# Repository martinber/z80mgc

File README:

z80mgc
======

z80 minimal game console

```
~/extra/async/programas/zasm-4.4.10-Linux64/zasm ./../../src/test.asm -l ./../../out/test.lst -o ./../../out/test.bin -uw; cargo run -- ../../out/test.bin
```

Clock speed
-----------

- RAM is 71256 SA25TPG. Therefore is 25ns access time: Data is valid 25ns after OE and CS are set.
- RAM is 28C64 25P. Therefore I think it is 250ns access time: Data is valid 250ns after OE and CS are set.
- CPU is Z84C0006TPG. Therefore is 6.17MHz, equivalent to 166ns per clock. It waits memory for 2
  clock cycles (this time is shortened a bit because of the logic gates I use to select memory).
- LCD takes 1.6ms for clearing and 72 µs (72000ns) for each of the other instructions. So I can do
  around 13800 instructions per second. When writing make the E pulse at least 160ns long (CPU does
  this for around 2 clock cycles) and leave the data for 20ns after disabling (CPU does this for
  around half a clock cycle). When reading, data is valid 260ns after enabled (CPU waits for around
  2 clock cycles)
- Logic gates have around 10ns propagation time.
- The nake game was doing around 150 instructions per game loop. If I consider 4 clocks per
  instruction, I can run it at 60fps if the clock is at around 36kHz?

So apparently I can run at full clock speed, where I would be close to reaching the limit of LCD
read times. I have to wait LCD after each instruction.

Other display options
---------------------

* LCD with HD44780: http://6502.org/mini-projects/optrexlcd/lcd.htm

* LCD with ST7920, allows graphics

* LCD with KS0108, allows graphics

* Nokia 5110

  * Parallel to serial

* ILI9163C display

  * Parallel to serial

* Composite video: http://www.cpuville.com/Projects/Standalone-Z80-computer/Standalone-Z80-home.html

  * Shift registers

  * Resistors and transistors

  * Precise clock

  * Precise delay tuning

* SOmething with AD722?

* Yamaha V9958, Yamaha V9938, Yamaha V9959, Yamaha V9990, Motorola 6845, Motorola 6847, TMS9918,

* Text only OSD chips: MAX7456

* Text only: Intel 8275 CRTC together with Intel 8257 DMA controller

* Composite video with a microcontroller?

* Composite video with ICs: https://www.chrismcovell.com/dottorikun.html#schematic

Sound
-----

* SN76489

Timing
------

* Mouser has Z80 timers

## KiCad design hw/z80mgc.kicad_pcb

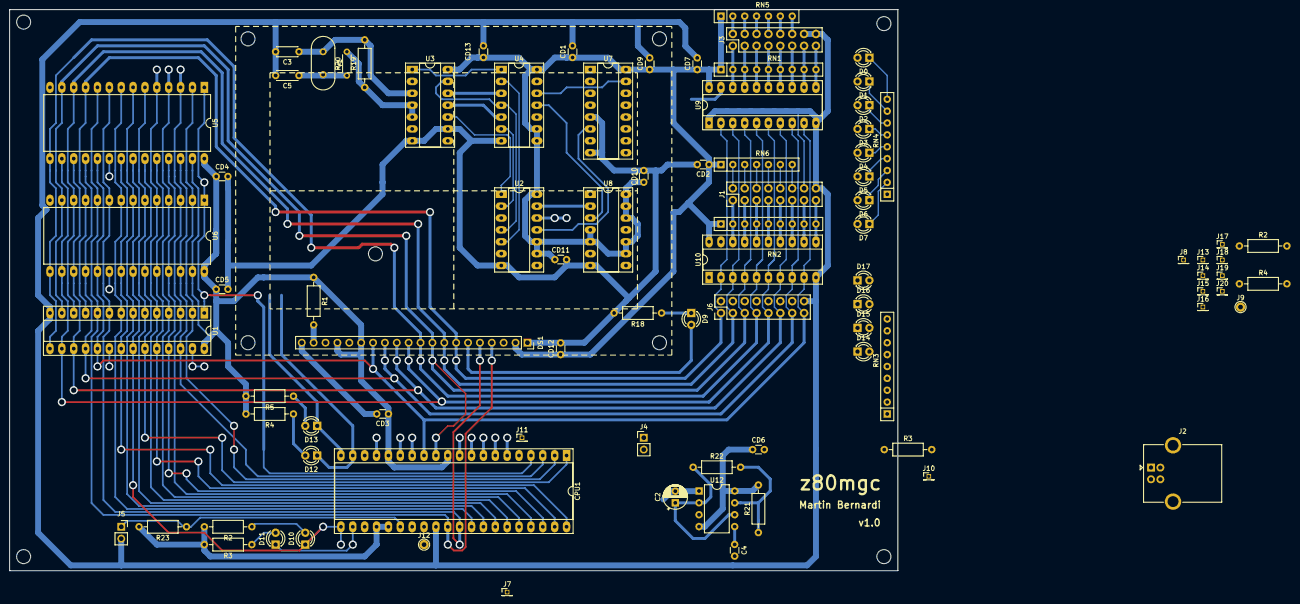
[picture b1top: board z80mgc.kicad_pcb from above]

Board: 4 copper layers, 190.0 x 120.0 mm, 87 parts (0 on the bottom side), 107 nets.

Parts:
C2: 1uF; CP_Radial_D5.0mm_P2.50mm
C3, C5: 33pF; C_Disc_D4.3mm_W1.9mm_P5.00mm
C4: 0.1uf; C_Disc_D3.0mm_W1.6mm_P2.50mm
CD1, CD2, CD3, CD5, CD6, CD7, CD9, CD10, CD11, CD12, CD13: 0.1uF; C_Disc_D3.0mm_W1.6mm_P2.50mm
CD4: F; C_Disc_D3.0mm_W1.6mm_P2.50mm
CPU1: Z80CPU; DIP-40_W15.24mm_Socket_LongPads
D0, D1, D2, D3, D4, D5, D6, D7, D9, D13, D14, D15, D16, D17: LED; LED_D3.0mm
D10: ~{RD}; LED_D3.0mm
D11: ~{WR}; LED_D3.0mm
D12: ~{MREQ}; LED_D3.0mm
DS1: QC12864B; QC12864B_Header
J1: IO_A; PinHeader_2x08_P2.54mm_Vertical
J2: USB_B; USB_B_OST_USB-B1HSxx_Horizontal
J3: IO_BTN; PinHeader_2x08_P2.54mm_Vertical
J4: POWER; PinHeader_1x02_P2.54mm_Vertical
J5: RESET; PinSocket_1x02_P2.54mm_Vertical
J6: IO_EXP; PinHeader_2x08_P2.54mm_Vertical
J7: ~{M1}; PinHeader_1x01_P1.27mm_Vertical
J8: ~{NMI}; PinHeader_1x01_P1.27mm_Vertical
J9: ~{HALT}; TestPoint_THTPad_D2.0mm_Drill1.0mm
J10: ~{WAIT}; PinHeader_1x01_P1.27mm_Vertical
J11: ~{CLK}; PinHeader_1x01_P1.27mm_Vertical
J12: ~{RFSH}; TestPoint_THTPad_D2.0mm_Drill1.0mm
J13: ~{RFSH}; PinHeader_1x01_P1.27mm_Vertical
J14: ~{BUSRQ}; PinHeader_1x01_P1.27mm_Vertical
J15: ~{RESET}; PinHeader_1x01_P1.27mm_Vertical
J16: ~{RD}; PinHeader_1x01_P1.27mm_Vertical
J17: ~{WR}; PinHeader_1x01_P1.27mm_Vertical
J18: ~{MREQ}; PinHeader_1x01_P1.27mm_Vertical
J19: ~{IORQ}; PinHeader_1x01_P1.27mm_Vertical
J20: ~{BUSACK}; PinHeader_1x01_P1.27mm_Vertical
R1, R2#2, R3#2, R4, R5, R18, R22, R23: 1k; R_Axial_DIN0207_L6.3mm_D2.5mm_P10.16mm_Horizontal
R2, R3, R4#2, R21: 10k; R_Axial_DIN0207_L6.3mm_D2.5mm_P10.16mm_Horizontal
R19: 100k; R_Axial_DIN0207_L6.3mm_D2.5mm_P10.16mm_Horizontal
R20: 260; R_Axial_DIN0204_L3.6mm_D1.6mm_P5.08mm_Horizontal
RN1, RN2: 10k; R_Array_SIP9
RN3, RN4: 1k; R_Array_SIP9
RN5, RN6: 1k; R_Array_SIP7
U1: 71256; DIP-28_W7.62mm_Socket_LongPads
U2: 74HC00; DIP-14_W7.62mm_Socket_LongPads
U3: 74HC04; DIP-14_W7.62mm_Socket_LongPads
U4: 74HC02; DIP-14_W7.62mm_Socket_LongPads
U5, U6: 28C256; DIP-28_W15.24mm_LongPads
U7: 74HC138; DIP-16_W7.62mm_Socket_LongPads
U8: 74HC86; DIP-14_W7.62mm_Socket_LongPads
U9, U10: 74HC245; DIP-20_W7.62mm_Socket_LongPads
U12: NE555P; DIP-8_W7.62mm
Y1: 6MHz; Crystal_HC49-4H_Vertical

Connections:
+5V: CD1.1, CD2.1, CD3.1, CD4.1, CD5.1, CD6.1, CD7.1, CD9.1, CD10.1, CD11.1, CD12.1, CD13.1, CPU1.11 (VCC), DS1.2 (VDD), DS1.15 (PSB), DS1.17 (RST), J2.1 (VBUS), J4.1, J6.11, R1.1, R2.1, R2#2.2, R3.1, R3#2.2, R4.2, R4#2.1, R5.2, R21.2, R23.2, RN1.1 (common), RN2.1 (common), RN3.1 (common), RN5.1 (common), RN6.1 (common), U1.28 (VCC), U2.9, U2.10, U2.14 (VCC), U3.14 (VCC), U4.8, U4.9, U4.14 (VCC), U5.27 (~WE), U5.28 (VCC), U6.27 (~WE), U6.28 (VCC), U7.16 (VCC), U8.4, U8.5, U8.9, U8.10, U8.12, U8.13, U8.14 (VCC), U9.20 (VCC), U10.20 (VCC), U12.4 (R), U12.8 (VCC)
ADDR0: CPU1.30 (A0), DS1.4 (RS), J6.10, U1.10 (A0), U5.10 (A0), U6.10 (A0)
ADDR1: CPU1.31 (A1), DS1.5 (R/W), U1.9 (A1), U5.9 (A1), U6.9 (A1), U8.1
ADDR2: CPU1.32 (A2), U1.8 (A2), U5.8 (A2), U6.8 (A2)
ADDR3: CPU1.33 (A3), U1.7 (A3), U5.7 (A3), U6.7 (A3)
ADDR4: CPU1.34 (A4), U1.6 (A4), U5.6 (A4), U6.6 (A4)
ADDR5: CPU1.35 (A5), U1.5 (A5), U5.5 (A5), U6.5 (A5), U7.3 (A2)
ADDR6: CPU1.36 (A6), U1.4 (A6), U5.4 (A6), U6.4 (A6), U7.2 (A1)
ADDR7: CPU1.37 (A7), U1.3 (A7), U5.3 (A7), U6.3 (A7), U7.1 (A0)
ADDR8: CPU1.38 (A8), U1.25 (A8), U5.25 (A8), U6.25 (A8)
ADDR9: CPU1.39 (A9), U1.24 (A9), U5.24 (A9), U6.24 (A9)
ADDR10: CPU1.40 (A10), U1.21 (A10), U5.21 (A10), U6.21 (A10)
ADDR11: CPU1.1 (A11), U1.23 (A11), U5.23 (A11), U6.23 (A11)
ADDR12: CPU1.2 (A12), U1.2 (A12), U5.2 (A12), U6.2 (A12)
ADDR13: CPU1.3 (A13), U1.26 (A13)
ADDR14: CPU1.4 (A14), U1.1 (A14), U2.5, U4.2
ADDR15: CPU1.5 (A15), U2.2, U4.6
DATA0: CPU1.14 (D0), D0.2 (A), DS1.7 (D0), J6.1, U1.11 (Q0), U5.11 (D0), U6.11 (D0), U9.2 (A0), U10.2 (A0)
DATA1: CPU1.15 (D1), D1.2 (A), DS1.8 (D1), J6.2, U1.12 (Q1), U5.12 (D1), U6.12 (D1), U9.3 (A1), U10.3 (A1)
DATA2: CPU1.12 (D2), D2.2 (A), DS1.9 (D2), J6.3, U1.13 (Q2), U5.13 (D2), U6.13 (D2), U9.4 (A2), U10.4 (A2)
DATA3: CPU1.8 (D3), D3.2 (A), DS1.10 (D3), J6.4, U1.15 (Q3), U5.15 (D3), U6.15 (D3), U9.5 (A3), U10.5 (A3)
DATA4: CPU1.7 (D4), D4.2 (A), DS1.11 (D4), J6.5, U1.16 (Q4), U5.16 (D4), U6.16 (D4), U9.6 (A4), U10.6 (A4)
DATA5: CPU1.9 (D5), D5.2 (A), DS1.12 (D5), J6.6, U1.17 (Q5), U5.17 (D5), U6.17 (D5), U9.7 (A5), U10.7 (A5)
DATA6: CPU1.10 (D6), D6.2 (A), DS1.13 (D6), J6.7, U1.18 (Q6), U5.18 (D6), U6.18 (D6), U9.8 (A6), U10.8 (A6)
DATA7: CPU1.13 (D7), D7.2 (A), DS1.14 (D7), J6.8, U1.19 (Q7), U5.19 (D7), U6.19 (D7), U9.9 (A7), U10.9 (A7)
DISP_EN: D9.2 (A), DS1.6 (E), U4.13
GND: C2.2, C3.2, C4.2, C5.2, CD1.2, CD2.2, CD3.2, CD4.2, CD5.2, CD6.2, CD7.2, CD9.2, CD10.2, CD11.2, CD12.2, CD13.2, CPU1.29 (GND), DS1.1 (VSS), DS1.20 (LED(-)), J1.9, J1.10, J2.4 (GND), J2.5 (Shield), J3.9, J3.10, J4.2, J5.2, J6.9, R18.2, RN4.1 (common), U1.14 (GND), U2.7 (GND), U3.7 (GND), U3.9, U4.7 (GND), U5.14 (GND), U7.5 (~E2), U7.8 (GND), U8.7 (GND), U9.1 (A->B), U9.10 (GND), U10.10 (GND), U12.1 (GND)
unnamed: C3.1, R19.2, U3.3, Y1.1
unnamed: C5.1, R20.1, Y1.2
unnamed: D0.1 (K), RN4.9 (R8)
unnamed: D1.1 (K), RN4.8 (R7)
unnamed: D2.1 (K), RN4.7 (R6)
unnamed: D3.1 (K), RN4.6 (R5)
unnamed: D4.1 (K), RN4.5 (R4)
unnamed: D5.1 (K), RN4.4 (R3)
unnamed: D6.1 (K), RN4.3 (R2)
unnamed: D7.1 (K), RN4.2 (R1)
unnamed: D9.1 (K), R18.1
unnamed: D10.2 (A), R2#2.1, RN3.2 (R1)
unnamed: D11.2 (A), R3#2.1, RN3.3 (R2)
unnamed: D12.2 (A), R4.1, RN3.4 (R3)
unnamed: D13.2 (A), R5.1, RN3.5 (R4)
unnamed: D14.2 (A), RN3.6 (R5)
unnamed: D15.2 (A), RN3.7 (R6)
unnamed: D16.2 (A), RN3.8 (R7)
unnamed: D17.2 (A), RN3.9 (R8)
unnamed: DS1.19 (LED(+)), R1.2
unnamed: J1.1, RN2.2 (R1), U10.18 (B0)
unnamed: J1.2, RN2.3 (R2), U10.17 (B1)
unnamed: J1.3, RN2.4 (R3), U10.16 (B2)
unnamed: J1.4, RN2.5 (R4), U10.15 (B3)
unnamed: J1.5, RN2.6 (R5), U10.14 (B4)
unnamed: J1.6, RN2.7 (R6), U10.13 (B5)
unnamed: J1.7, RN2.8 (R7), U10.12 (B6)
unnamed: J1.8, RN2.9 (R8), U10.11 (B7)
unnamed: J1.11, RN6.7 (R6)
unnamed: J1.12, RN6.6 (R5)
unnamed: J1.13, RN6.5 (R4)
unnamed: J1.14, RN6.4 (R3)
unnamed: J1.15, RN6.3 (R2)
unnamed: J1.16, RN6.2 (R1)
unnamed: J3.1, RN1.2 (R1), U9.18 (B0)
unnamed: J3.2, RN1.3 (R2), U9.17 (B1)
unnamed: J3.3, RN1.4 (R3), U9.16 (B2)
unnamed: J3.4, RN1.5 (R4), U9.15 (B3)
unnamed: J3.5, RN1.6 (R5), U9.14 (B4)
unnamed: J3.6, RN1.7 (R6), U9.13 (B5)
unnamed: J3.7, RN1.8 (R7), U9.12 (B6)
unnamed: J3.8, RN1.9 (R8), U9.11 (B7)
unnamed: J3.11, RN5.7 (R6)
unnamed: J3.12, RN5.6 (R5)
unnamed: J3.13, RN5.5 (R4)
unnamed: J3.14, RN5.4 (R3)
unnamed: J3.15, RN5.3 (R2)
unnamed: J3.16, RN5.2 (R1)
unnamed: J6.15, U7.11 (~Y4)
unnamed: J6.16, U7.12 (~Y3)
unnamed: R19.1, R20.2, U3.4, U3.5
unnamed: U2.1, U3.10
unnamed: U2.4, U3.13, U4.4
unnamed: U3.12, U4.3
unnamed: U4.11, U8.3
unnamed: U3.2, U5.20 (~CS)
unnamed: U2.11, U7.6 (E3)
unnamed: U4.12, U7.15 (~Y0)
unnamed: U7.14 (~Y1), U9.19 (CE)
unnamed: U7.13 (~Y2), U10.19 (CE)
unnamed: C4.1, U12.5 (CV)
unnamed: R21.1, R22.2, U12.7 (DIS)
unnamed: C2.1, R22.1, U12.2 (TR), U12.6 (THR)
~BUSACK: CPU1.23 (~BUSACK), J20.1
~BUSRQ: CPU1.25 (~BUSRQ), J14.1, R4#2.2
~CLK: CPU1.6 (~CLK), J11.1, U3.6
~HALT: CPU1.18 (~HALT), J9.1
~INT: CPU1.16 (~INT), J13.1, R2.2
~IORQ: CPU1.20 (~IORQ), D13.1 (K), J6.12, J19.1, U7.4 (~E1)
~M1: CPU1.27 (~M1), J7.1
~MREQ: CPU1.19 (~MREQ), D12.1 (K), J18.1, U3.11, U4.5
~NMI: CPU1.17 (~NMI), D14.1 (K), J8.1, U12.3 (Q)
~RAM1_EN: D15.1 (K), U1.20 (~CS), U2.3
~RD: CPU1.21 (~RD), D10.1 (K), J6.14, J16.1, U1.22 (~OE), U2.12, U5.22 (~OE), U6.22 (~OE), U10.1 (A->B)
~RESET: CPU1.26 (~RESET), J5.1, J15.1, R23.1
~RFSH: CPU1.28 (~RFSH), J12.1
~ROM1_EN: D16.1 (K), U3.1, U4.1
~ROM2_EN: D17.1 (K), U2.6, U6.20 (~CS)
~WAIT: CPU1.24 (~WAIT), J10.1, R3.2
~WR: CPU1.22 (~WR), D11.1 (K), J6.13, J17.1, U1.27 (~WE), U2.13, U8.2

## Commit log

2023-01-07 Using iz80 emulator
2023-01-08 Work on snake game
2023-01-08 Fix NMI handler memory location
2023-01-08 Adding GUI
2023-01-19 Add screen
2023-01-20 Add keyboard input to emulator and implement input in snake game
2023-01-20 Implement food and game over
2023-01-21 PRNG and food placing, finished the game I think
2023-02-13 Starting LCD emulator and was able to make LCD work with test.asm
2023-02-16 Was able to draw something with cairo
2023-02-17 LCD emulator starting to work
2023-02-18 Snake and test running on hardware
2023-02-18 Nearest neighbor interpolation for LCD emualtion
2023-02-21 Reorganizing snake and starting to make graphical version
2023-02-22 Graphic LCD emulation working
2023-02-22 Graphic LCD code working
2023-02-22 Wait for LCD
2023-03-05 Render snake game with graphics
2023-04-01 Separating assembly for each game
2023-04-02 Startin with bricks
2023-04-02 Improving timing and documentation
2023-04-02 Timing working for snake
2023-04-28 Start designing circuit and added trace toggle
2023-05-01 Bricks being drawn
2023-05-01 Allow to enable trace from asm code
2023-05-01 Copy level data to RAM
2023-05-01 Starting to draw ball
2023-05-01 Starting drawing pad
2023-05-01 Drawing pad of length 2
2023-05-06 Clear old ball graphic before moving
2023-05-07 Efficient vertical clear old ball graphic before moving
2023-05-07 Draw ball clearing only horizontally
2023-05-08 Several fixes but realized I have to clear ball before powerups and I need 1px ball
2023-05-08 Fixed ball clearing and collision
2023-05-12 Pad and bound colission
2023-05-14 Work on scmenatic and PCB
2023-05-23 Limit pad movement
2023-05-23 Integrate the test program into the rest
2023-05-23 Test in HW, realized the display emulator is wrong
2023-05-23 Update gramn addresses in LCD emulator
2023-05-24 Fix check program
2023-09-17 Snake working with framebuffer
2023-09-17 Clear framebuffer when resetting snake
2023-09-26 Fix snake movement bugs
2024-02-03 Lots of work on Kicad, and gave up on PCB
2024-02-06 Fixed EEPROM programmer
2024-02-15 CRC32 for EEPROM programmer
2024-02-17 Starting welcome screen
2024-02-25 Update emulator input and finish welcome.asm visual
2024-02-25 Fix emulator A button and launch game from welcome.asm
2024-02-25 Fix buttons in snake game
2024-02-25 Fix jump table
2024-02-25 Move framebuffer code to z80mgc.asm
2024-03-10 Draw bricks with fbuf, modify fbuf code in general
2024-03-10 Draw pad and fix movement of pad
2024-03-24 Draw ball
2024-03-24 Bricks game working but slow
2024-03-25 Draw only necessary lines in board game
2024-12-04 Design the box
2024-12-08 Version v1.0.0
